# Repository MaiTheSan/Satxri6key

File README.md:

# Satxri6key
Commission Keyboard 6Key for osu!
* Hotswap
* RGB Perkey
* Atmega32U4
* Can add Oled 0.91 monitor
## Description
* Opensource PCB
* Kicad requirement 
## Layout

## PCB

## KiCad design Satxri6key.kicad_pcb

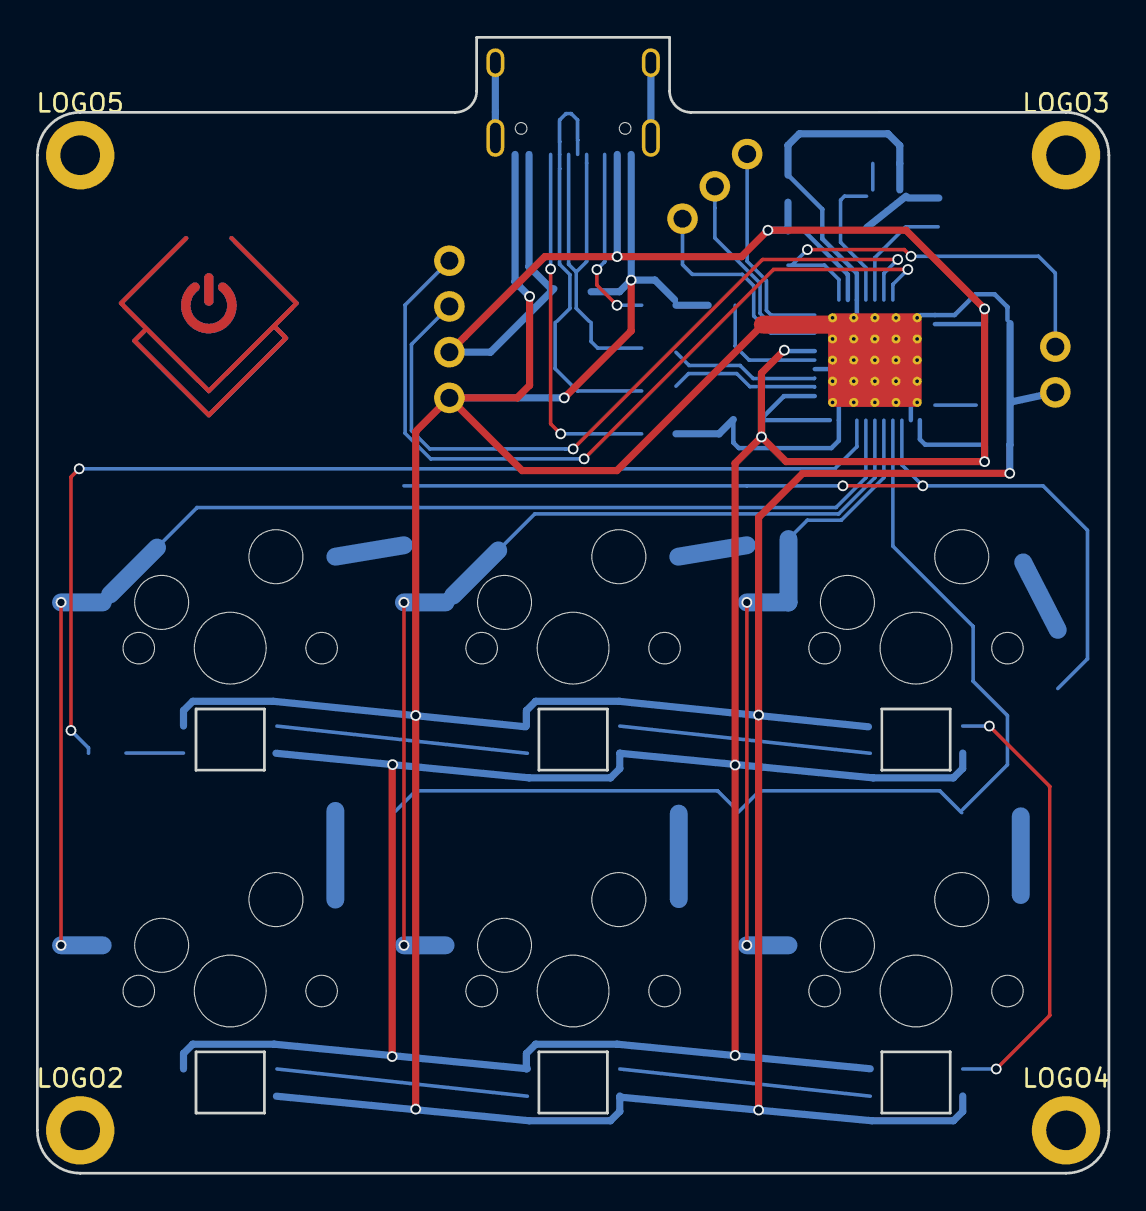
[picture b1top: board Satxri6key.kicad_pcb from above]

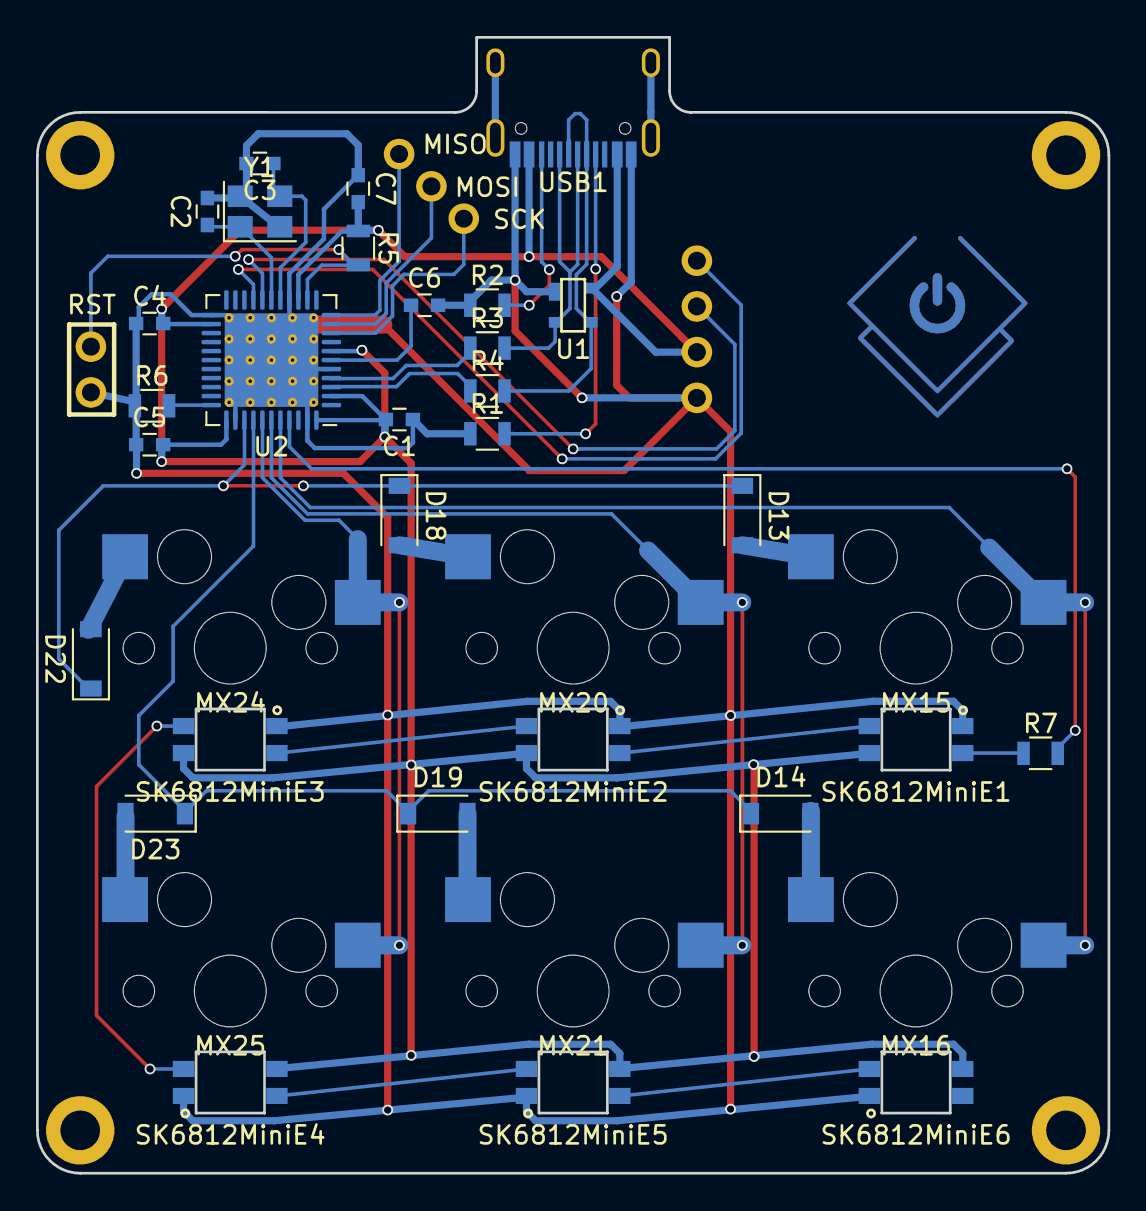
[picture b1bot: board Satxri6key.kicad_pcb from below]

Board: 2 copper layers, 59.5 x 63.1 mm, 44 parts (33 on the bottom side), 36 nets.

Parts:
C1: 10uF; C_0603
C2, C3: 22pF; C_0603
C4, C5, C7: 0.1uF; C_0603
C6: 1uF; C_0603
D13, D14, D18, D19, D22, D23: D; D_SOD-123
LOGO1: Logo_Open_Hardware_Large; sanpjxlogo-PCB-type
LOGO2, LOGO3, LOGO4, LOGO5: Logo_Open_Hardware_Large; MountingHole_2.2mm_M2_DIN965_Pad
MX15, MX16, MX20, MX21, MX24, MX25: MX-NoLED; MXOnly-1U-Hotswap
R1, R2: 5.1k; R_0805
R3, R4: 22; R_0805
R5: 10k; R_0805
R6: 1k; R_0805
R7: R; R_0805
SK6812MiniE1, SK6812MiniE2, SK6812MiniE3: WS2812B; RGB-6028_FLIPPED
SK6812MiniE4, SK6812MiniE5, SK6812MiniE6: WS2812B; RGB-6028
U1: PRTR5V0U2X; SOT143B
U2: ATmega32U4-MU; QFN-44-1EP_7x7mm_P0.5mm_EP5.2x5.2mm_ThermalVias
U3: STF202-22T1G; 0.91_SSD1306_OLED
U4, U5: STF202-22T1G; Reset_Pretty
USB1: HRO-TYPE-C-31-M-12; HRO-TYPE-C-31-M-12-Assembly
Y1: 16Mhz; Crystal_SMD_3225-4Pin_3.2x2.5mm

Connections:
+5V: C1.2, C4.2, C5.2, C7.2, R5.1, SK6812MiniE1.1, SK6812MiniE2.1, SK6812MiniE3.1, SK6812MiniE4.1, SK6812MiniE5.1, SK6812MiniE6.1, U1.4, U2.2, U2.7, U2.14, U2.24, U2.34, U2.44, U3.2, USB1.2, USB1.11
COL0: MX15.1, MX16.1, U2.40
COL1: MX20.1, MX21.1, U2.39
COL2: MX24.1, MX25.1, U2.38
D+: R3.1, U2.4
D-: R4.1, U2.3
GND: C1.1, C2.2, C3.2, C4.1, C5.1, C6.2, C7.1, R1.1, R2.1, R6.1, SK6812MiniE1.3, SK6812MiniE2.3, SK6812MiniE3.3, SK6812MiniE4.3, SK6812MiniE5.3, SK6812MiniE6.3, U1.1, U2.5, U2.15, U2.23, U2.35, U2.43, U2.45, U3.1, U5.6, USB1.1, USB1.12, USB1.13, Y1.2, Y1.4
MISO: U2.11, U4.1
MOSI: U2.10, U4.3
unnamed: C2.1, U2.17, Y1.1
unnamed: C3.1, U2.16, Y1.3
unnamed: C6.1, U2.6
unnamed: D13.2, MX15.2
unnamed: D14.2, MX16.2
unnamed: D18.2, MX20.2
unnamed: D19.2, MX21.2
unnamed: D22.2, MX24.2
unnamed: D23.2, MX25.2
unnamed: R1.2, USB1.4
unnamed: R2.2, USB1.10
unnamed: R3.2, U1.2, USB1.6, USB1.8
unnamed: R4.2, U1.3, USB1.5, USB1.7
unnamed: R6.2, U2.33
unnamed: R7.2, U2.41
unnamed: SK6812MiniE1.2, SK6812MiniE2.4
unnamed: SK6812MiniE2.2, SK6812MiniE3.4
unnamed: SK6812MiniE3.2, SK6812MiniE4.4
unnamed: SK6812MiniE4.2, SK6812MiniE5.4
unnamed: SK6812MiniE5.2, SK6812MiniE6.4
RGBLED: R7.1, SK6812MiniE1.4
ROW0: D13.1, D18.1, D22.1, U2.36
ROW1: D14.1, D19.1, D23.1, U2.37
RST: R5.2, U2.13, U5.5
SCK: U2.9, U4.2
SCL: U2.18, U3.3
SDA: U2.19, U3.4
